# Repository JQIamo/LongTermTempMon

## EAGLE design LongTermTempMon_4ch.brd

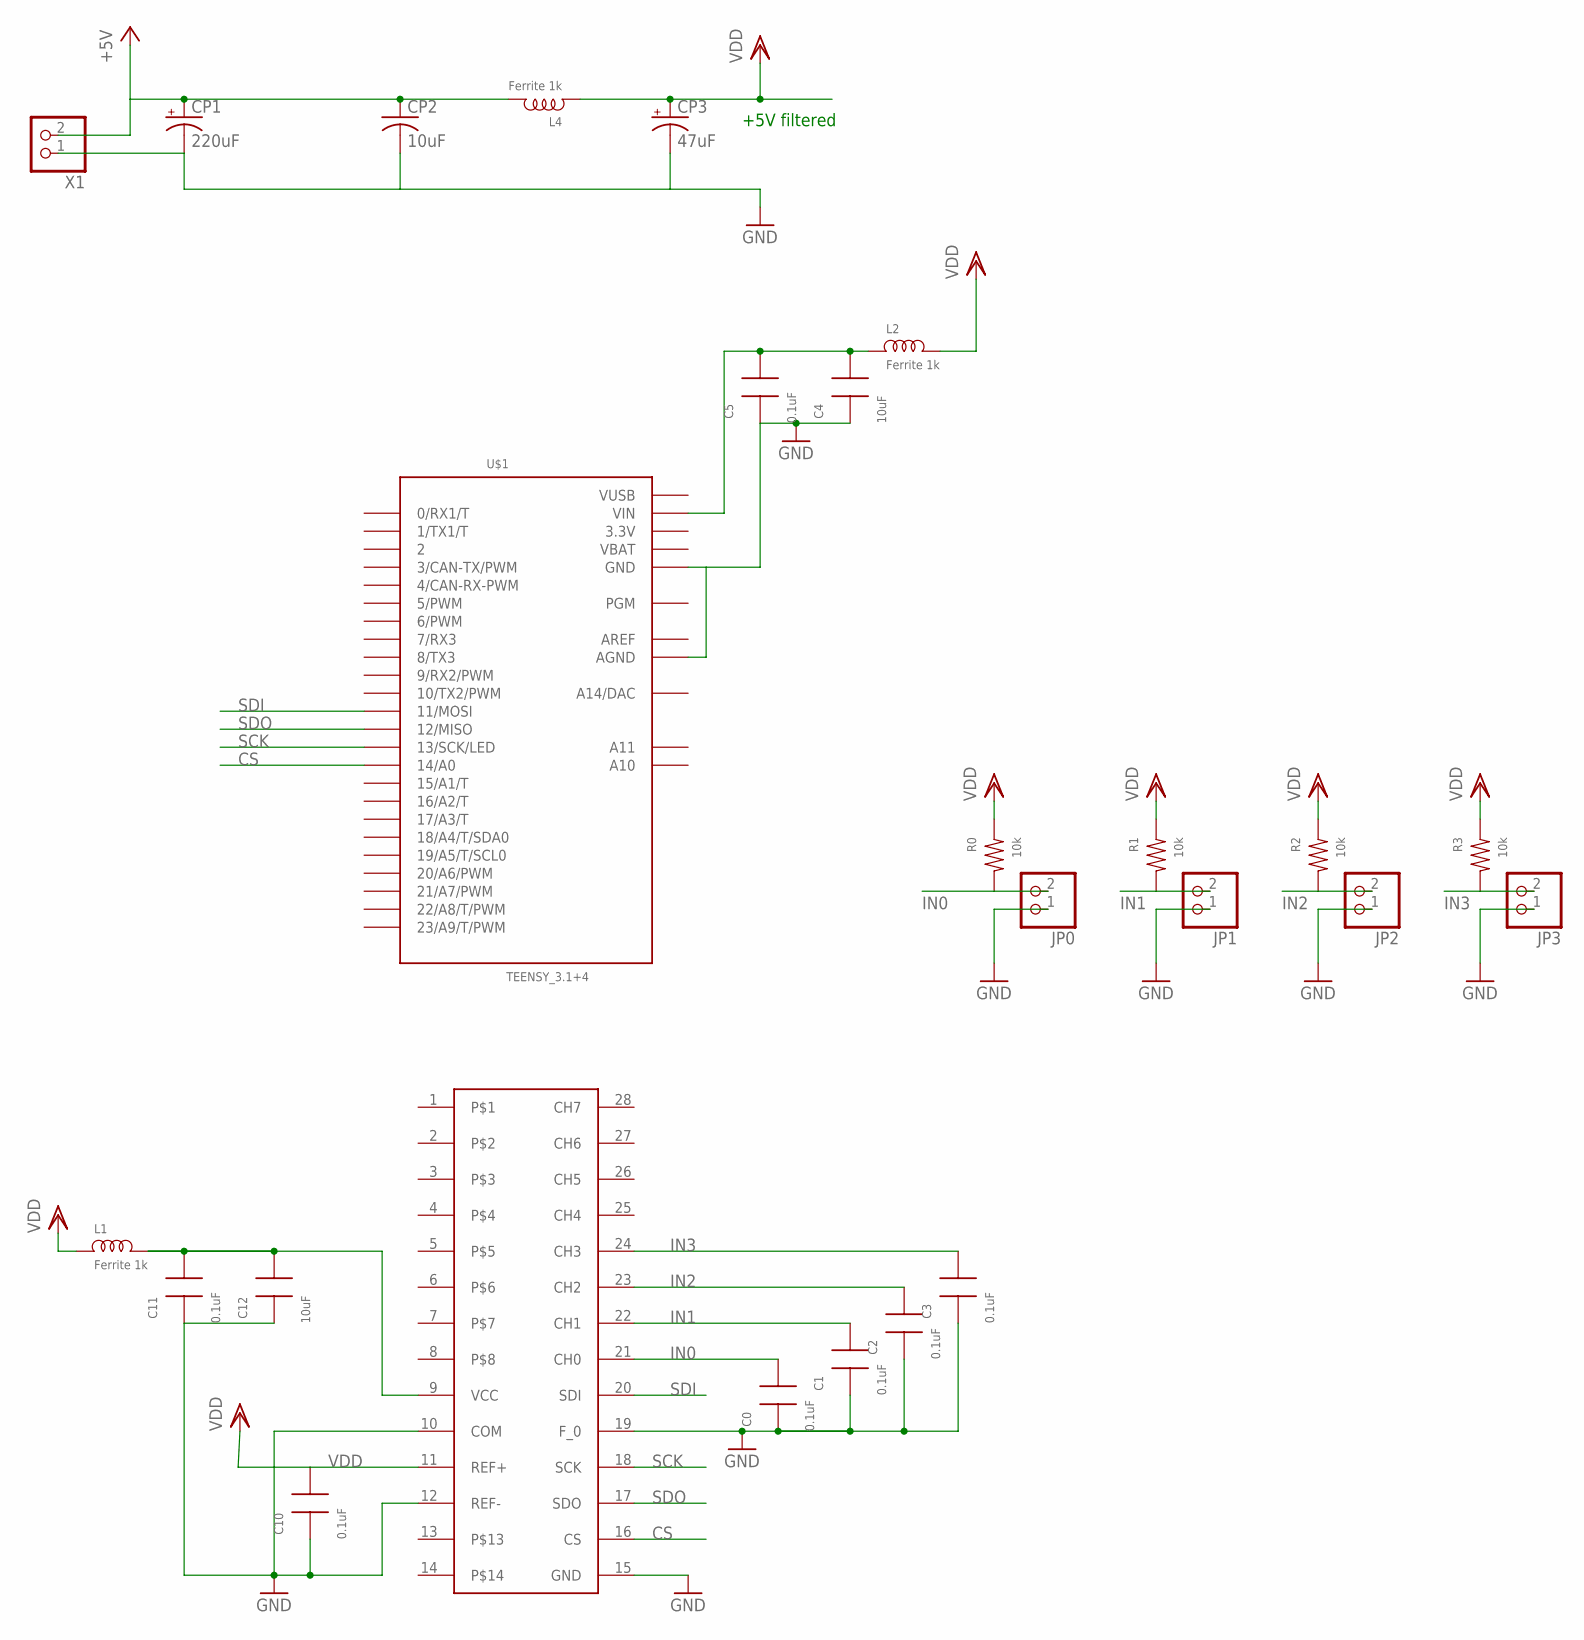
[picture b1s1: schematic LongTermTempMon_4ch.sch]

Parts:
C0, C1, C2, C3, C5, C10, C11: 0.1uF; 0603
C4, C12: 10uF; 0805
CP1: 220uF; PANASONIC_F
CP2: 10uF; C0805K
CP3: 47uF; CT7343
IC2: LTC2418; SSOP28
JP0, JP1, JP2, JP3: SCRWTRM-1X2; 1X02_SCRWTRM
L1, L2, L4: Ferrite 1k; 0805
R0, R1, R2, R3: 10k; 1206
U$1: TEENSY_3.1+4
X1: SCRWTRM-1X2; 1X02_SCRWTRM

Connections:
3.3V: U$1.3.3V, U$1.3.3V1 (3.3V)
+5V: CP1.+, CP2.1, L4.2, X1.2
AREF: U$1.AREF
CS: IC2.16 (CS), U$1.14/A0
GND: C0.1, C1.1, C2.1, C3.1, C4.1, C5.1, C10.1, C11.1, C12.1, CP1.-, CP2.2, CP3.-, IC2.10 (COM), IC2.12 (REF-), IC2.15 (GND), IC2.19 (F_0), JP0.1, JP1.1, JP2.1, JP3.1, U$1.AGND, U$1.GND, U$1.GND1 (GND), X1.1
IN0: C0.2, IC2.21 (CH0), JP0.2, R0.2
IN1: C1.2, IC2.22 (CH1), JP1.2, R1.2
IN2: C2.2, IC2.23 (CH2), JP2.2, R2.2
IN3: C3.2, IC2.24 (CH3), JP3.2, R3.2
unnamed: C11.2, C12.2, IC2.9 (VCC), L1.2
unnamed: C4.2, C5.2, L2.1, U$1.VIN
SCK: IC2.18 (SCK), U$1.13 (13/SCK/LED)
SDI: IC2.20 (SDI), U$1.11 (11/MOSI)
SDO: IC2.17 (SDO), U$1.12 (12/MISO)
VBAT: U$1.VBAT
VDD: C10.2, CP3.+, IC2.11 (REF+), L1.1, L2.2, L4.1, R0.1, R1.1, R2.1, R3.1
VUSB: U$1.VUSB

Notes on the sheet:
+5V filtered

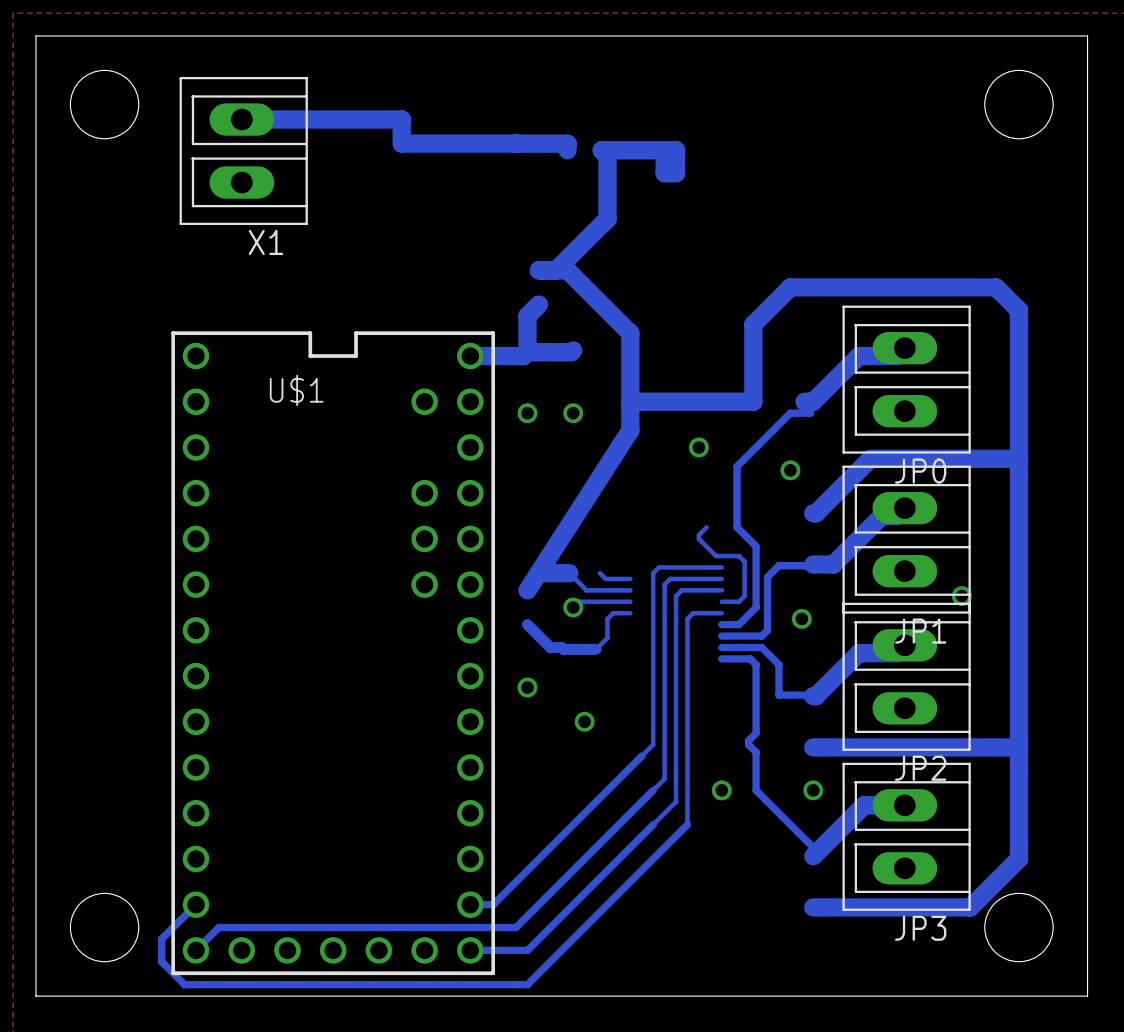
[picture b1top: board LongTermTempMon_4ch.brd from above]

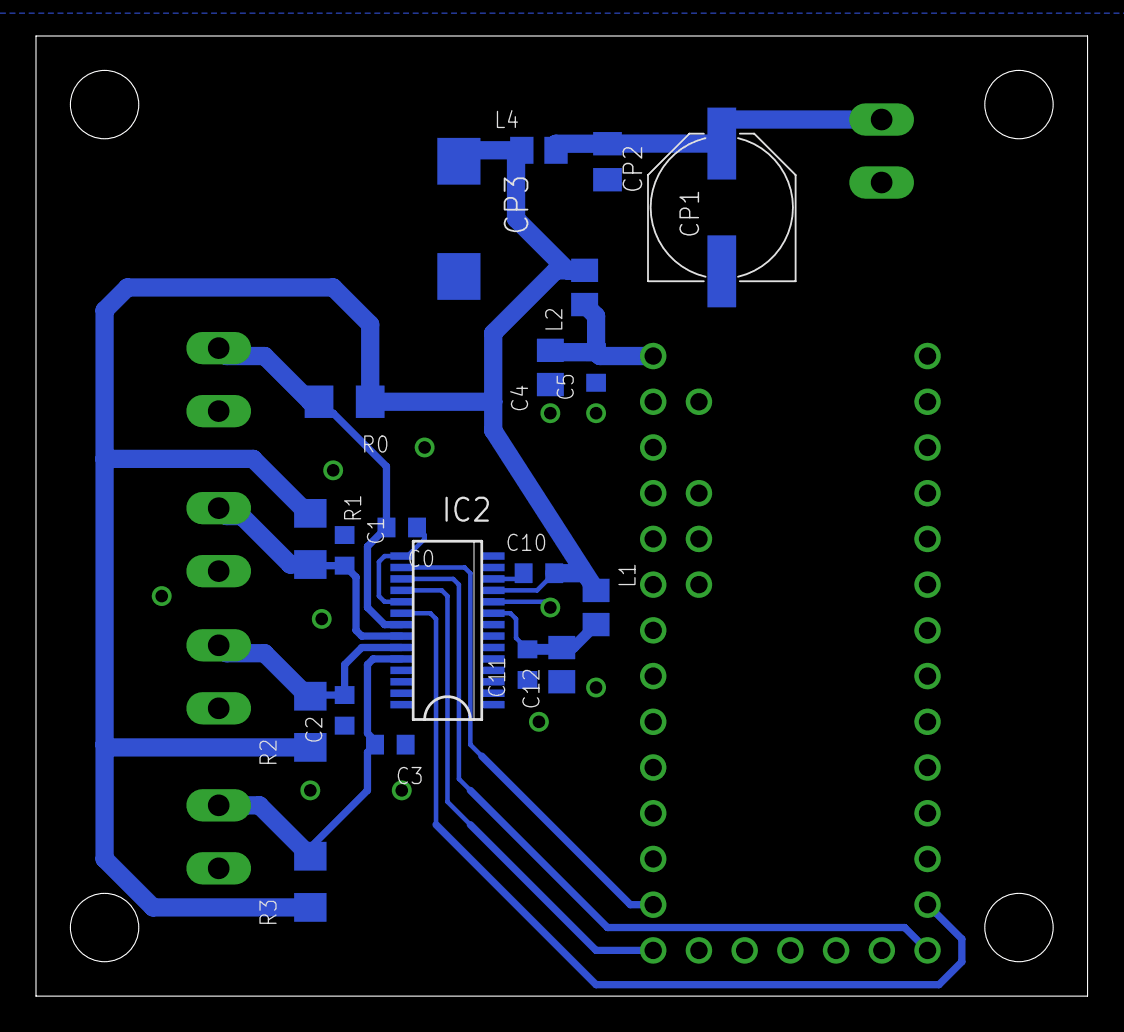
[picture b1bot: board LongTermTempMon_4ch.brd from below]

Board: 2 copper layers, 58.4 x 53.3 mm, 26 parts (20 on the bottom side), 14 nets.

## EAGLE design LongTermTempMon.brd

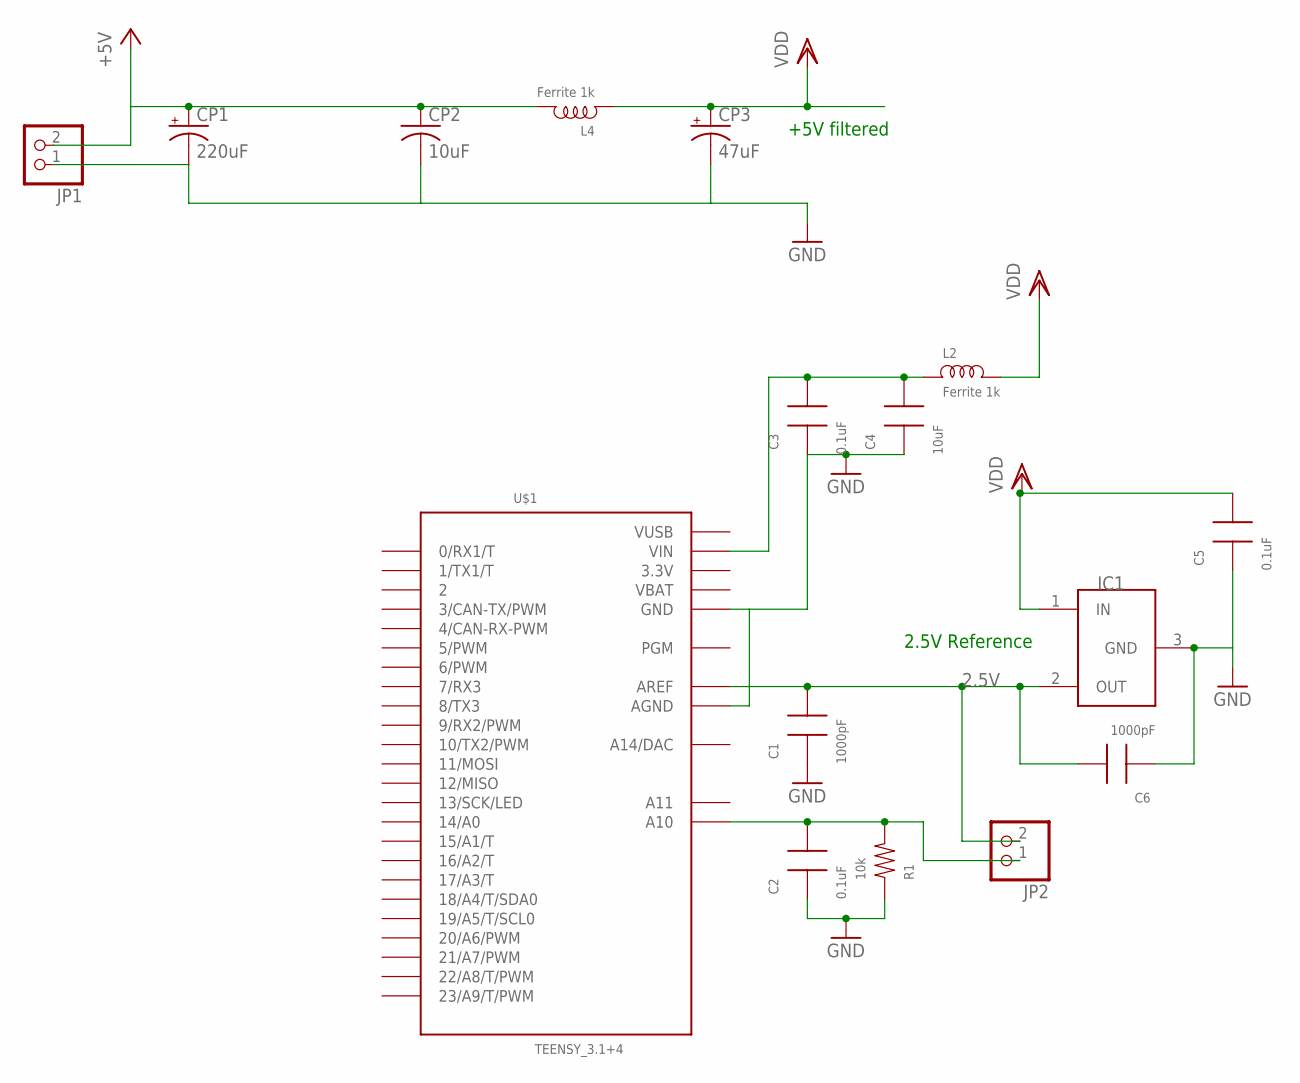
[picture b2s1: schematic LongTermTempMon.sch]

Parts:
C1, C6: 1000pF; 0603
C2, C3, C5: 0.1uF; 0603
C4: 10uF; 0805
CP1: 220uF; PANASONIC_F
CP2: 10uF; C0805K
CP3: 47uF; CT7343
IC1: TS6001; SOT-23
JP1, JP2: SCRWTRM-1X2; 1X02_SCRWTRM
L2, L4: Ferrite 1k; 0805
R1: 10k; 1206
U$1: TEENSY_3.1+4

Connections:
2.5V: C1.2, C6.2, IC1.2 (OUT), JP2.2, U$1.AREF
3.3V: U$1.3.3V, U$1.3.3V1 (3.3V)
+5V: CP1.+, CP2.1, JP1.2, L4.2
GND: C1.1, C2.1, C3.1, C4.1, C5.1, C6.1, CP1.-, CP2.2, CP3.-, IC1.3 (GND), JP1.1, R1.1, U$1.AGND, U$1.GND, U$1.GND1 (GND)
unnamed: C2.2, JP2.1, R1.2, U$1.A10
unnamed: C3.2, C4.2, L2.1, U$1.VIN
VBAT: U$1.VBAT
VDD: C5.2, CP3.+, IC1.1 (IN), L2.2, L4.1
VUSB: U$1.VUSB

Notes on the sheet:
2.5V Reference
+5V filtered

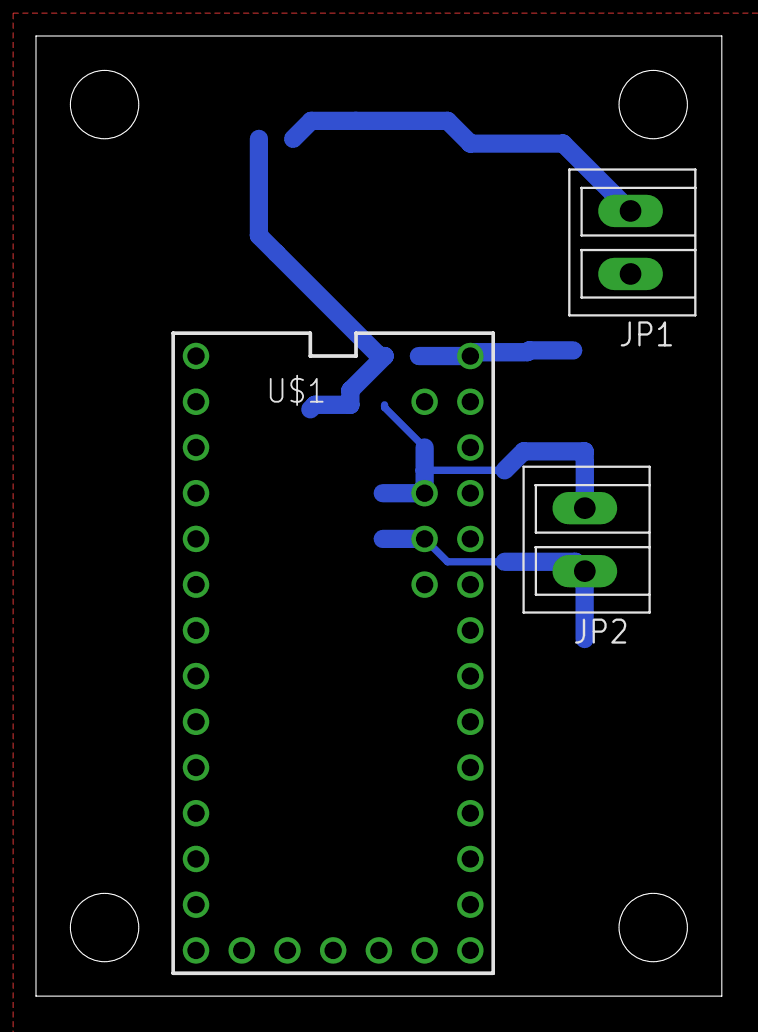
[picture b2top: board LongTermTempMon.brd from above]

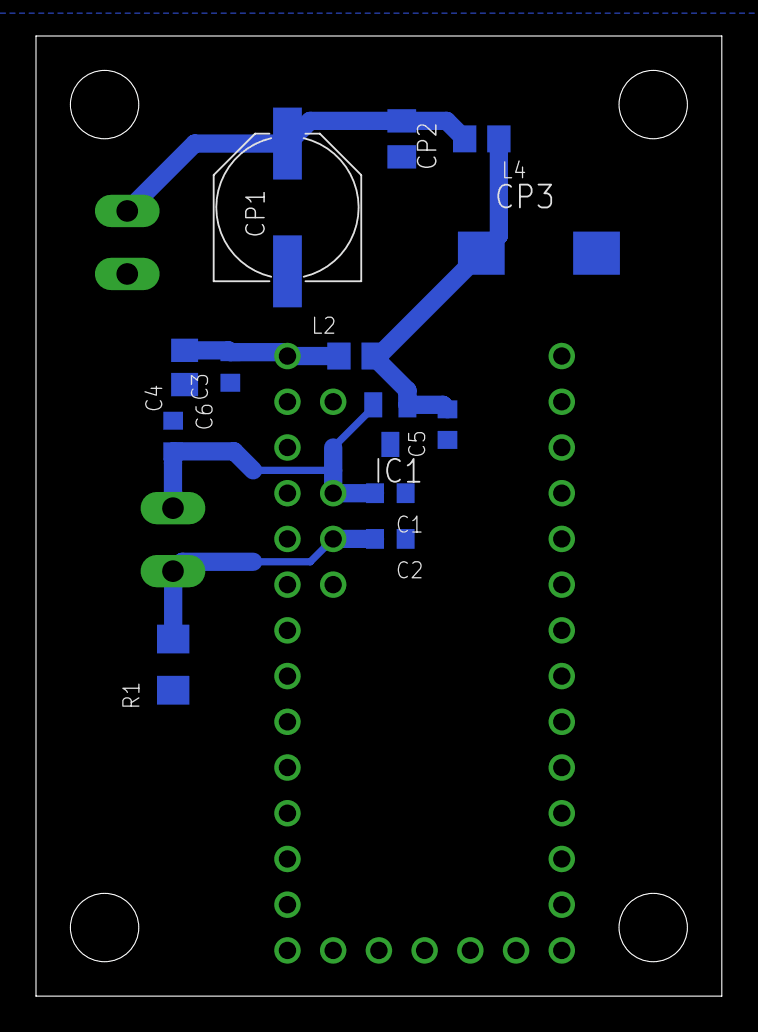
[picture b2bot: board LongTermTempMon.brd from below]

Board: 2 copper layers, 38.1 x 53.3 mm, 16 parts (13 on the bottom side), 7 nets.

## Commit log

2015-11-16 :neckbeard: Added .gitattributes & .gitignore files
2015-11-16 Single Channel, low res version
    Originoal version is just one channel and uses the internal ADC of the
    teensy
2015-11-16 Add 4 channel, high res version
    This version has more channels (4, though could be more) and an external
    ADC chip (LTC2418) with 24 bit resolution and up to 16 channels)
2015-11-16 Modified circuit to have reference resistor tied to +5V instead of Gnd
2015-12-28 Start Arduino sketch
2015-12-29 Arduino code working, needs calibration
2015-12-30 Added function that correctly reads to commanded channel
